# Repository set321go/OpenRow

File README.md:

# OpenRow

A project to design an build an open source rowing computer. This project was born from the idea that I would rather throw something cheaper than a cell phone into the water, a secondary driver was how expensive existing options are given they are in effect a specialized pedometer.

## Goals

1. Hardware and software for an acceleration based rowing computer similar in functionality to a variety of apps available for phones.
2. Speaker/Headset module integration (module provides headset functionality existing computer provides rowing data), which fits into existing headset amplifier form factor.
3. GPS & Bluetooth
4. Fitness platform compatability.

## Secondary Goals

1. Floats
2. Impeller Integration

## Design

This is purely a personal hobby project at some point it may make sense to use a funding platform to do a medium sized run with assembly but there are no plans for this. I have no background in EE.

### Circuit

I have used kicad 5. Its free and open source, you can use whatever tools you wish but you need to ensure the files in the project remain comatible with kicad.

### PCB

The current design is built to [JLCPCB](https://jlcpcb.com/capabilities/Capabilities) 2 layer design rules, I have no solution for providing multiple pcb's which would allow designs for multiple fabrictors. It is likely in the future to ease the design of RF components I will move to a 4 layer design.

### Assembly

Stencil and hand assembly with a homebrew toaster oven reflow setup for prototyping and testing.

### Case

3D printed - in progress

### Software

In progress

## Commercial Use

If you use this project commercially reference to its usage on the consumer device is desired but not required under the licensing terms.

## Getting Involved

If you would like to get involved please get in touch.

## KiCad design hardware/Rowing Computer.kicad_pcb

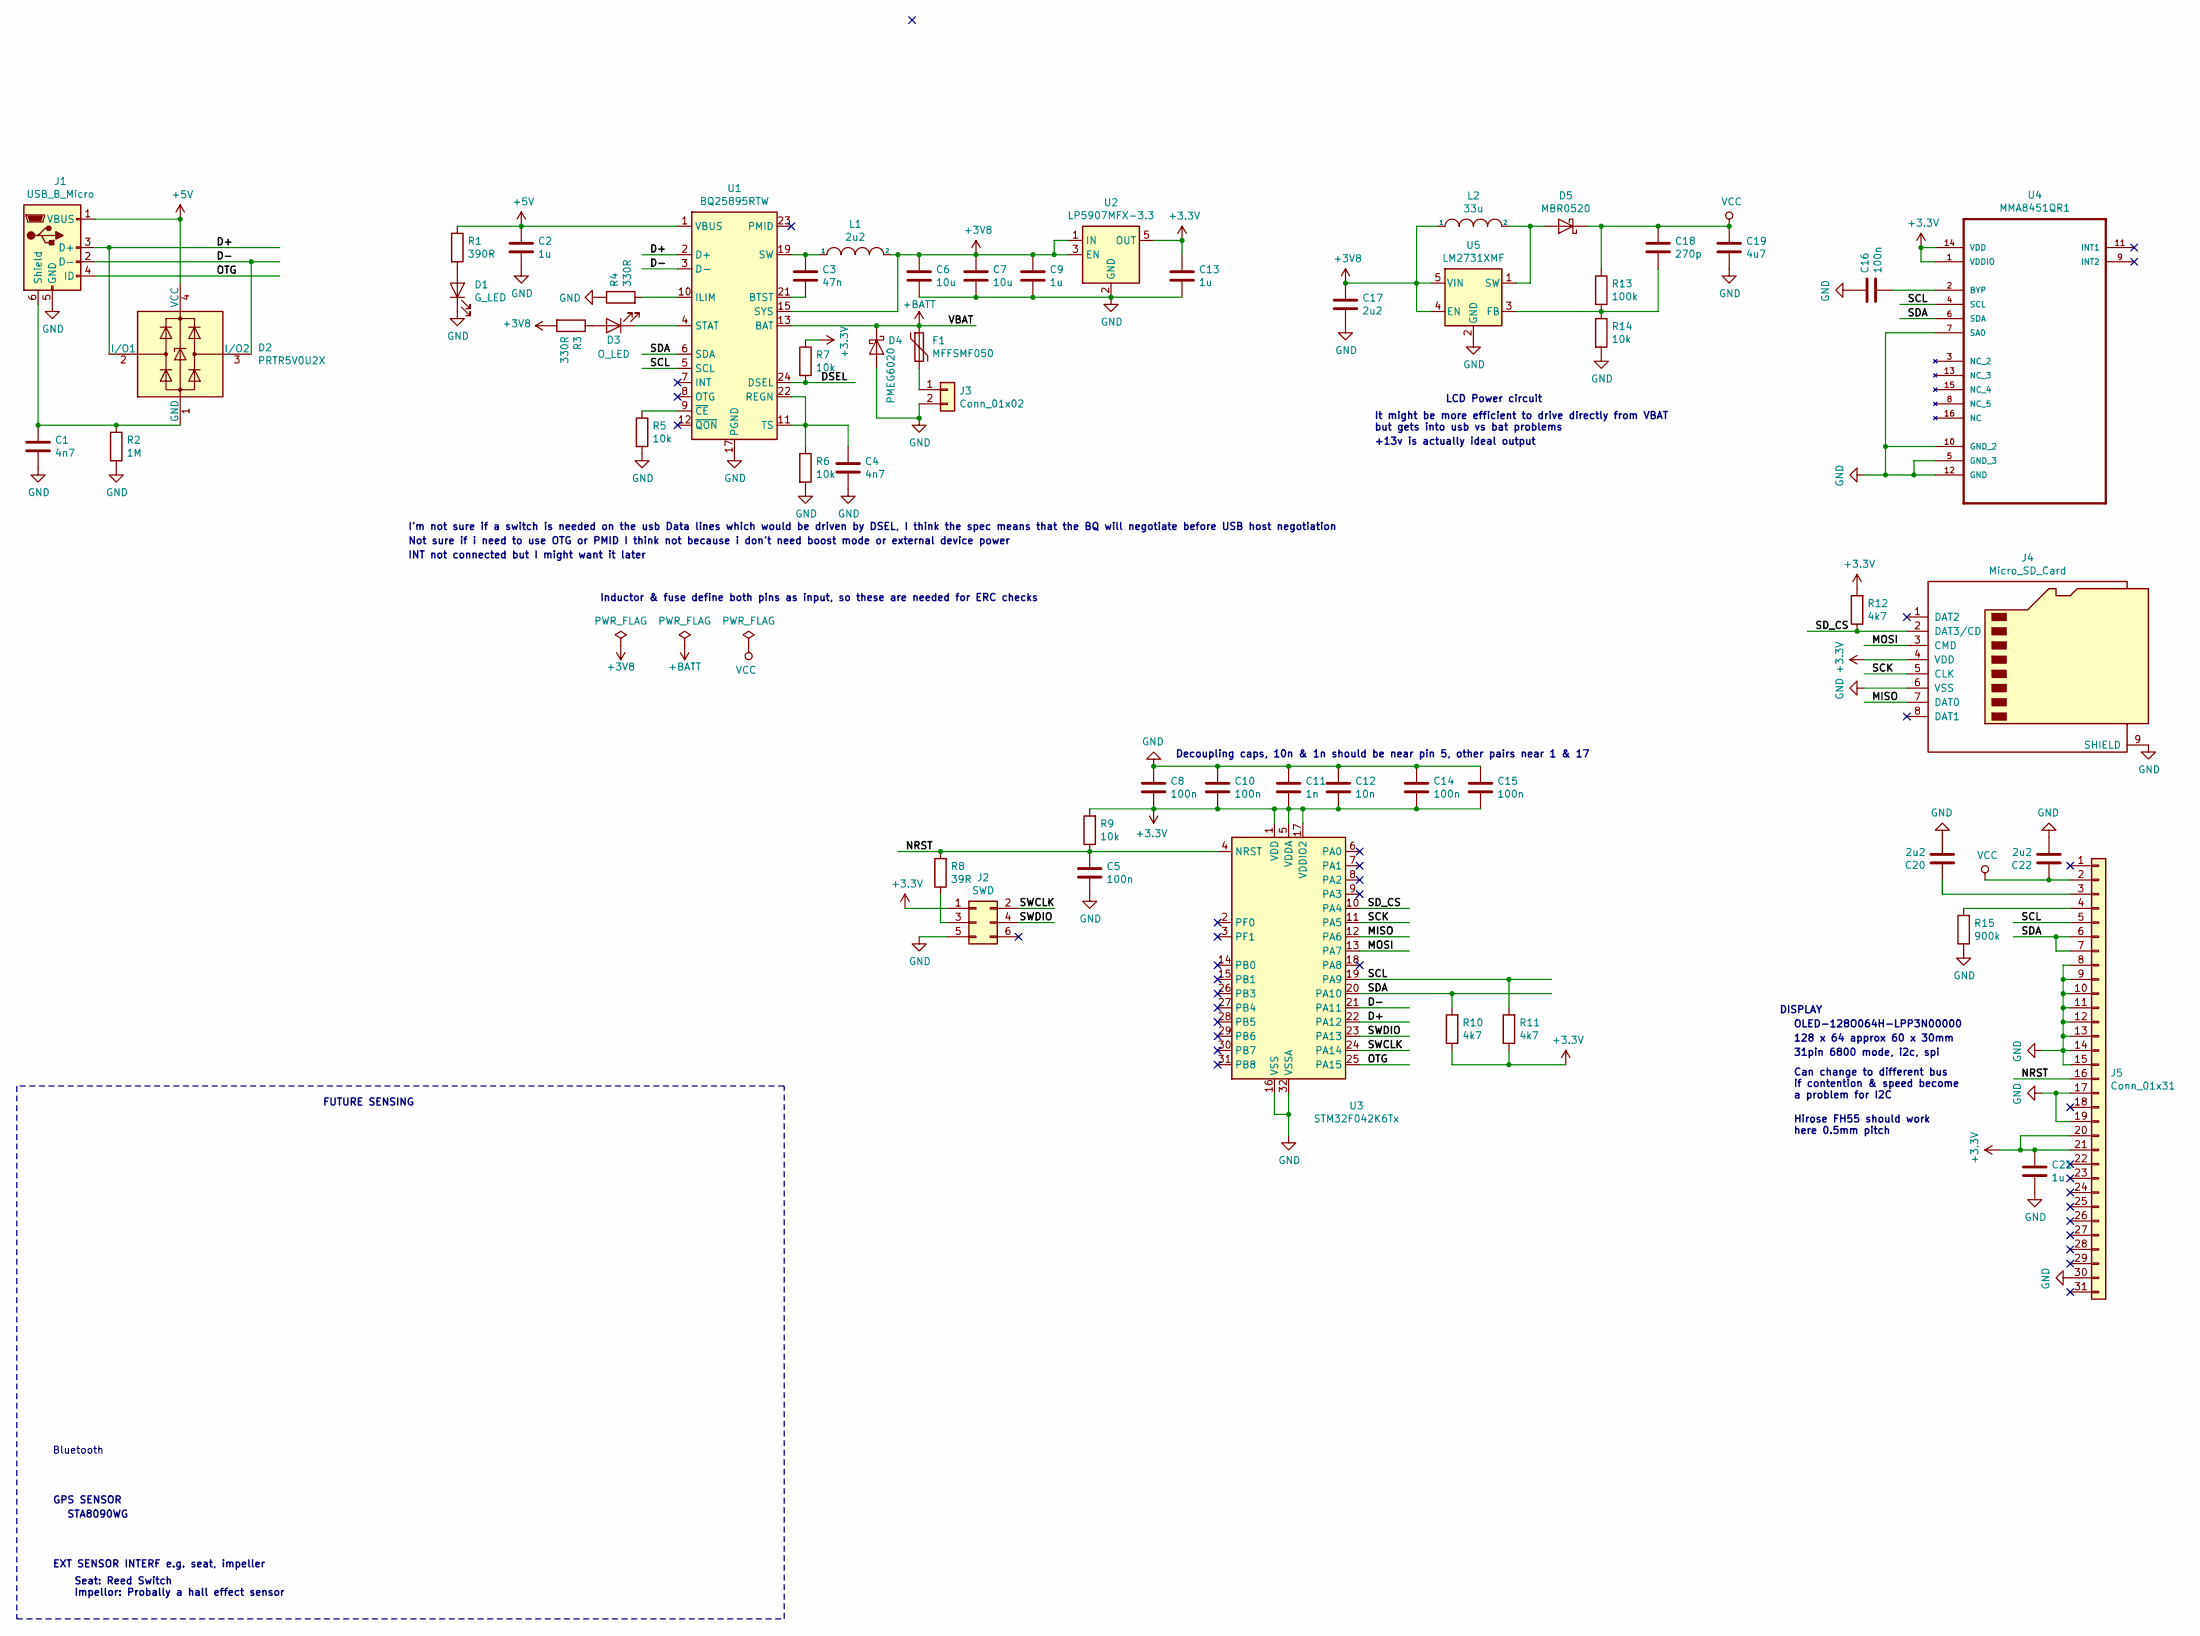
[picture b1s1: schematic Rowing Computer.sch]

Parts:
C1, C4: 4n7; C_0402_1005Metric
C2, C9, C13, C21: 1u; C_0402_1005Metric
C3: 47n; C_0402_1005Metric
C5, C8, C10, C14, C15, C16: 100n; C_0402_1005Metric
C6, C7: 10u; C_0603_1608Metric
C11: 1n; C_0402_1005Metric
C12: 10n; C_0402_1005Metric
C17, C20, C22: 2u2; C_0402_1005Metric
C18: 270p; C_0402_1005Metric
C19: 4u7; C_0603_1608Metric
D1: G_LED; LED_0402_1005Metric
D2: PRTR5V0U2X; SOT-143
D3: O_LED; LED_0402_1005Metric
D4: PMEG6020; D_SOD-123
D5: MBR0520; D_SOD-123
F1: MFFSMF050; Fuse_0402_1005Metric
J1: USB_B_Micro; USB_Micro-B_Molex_47346-0001
J2: SWD; PinHeader_2x03_P1.27mm_Vertical_SMD
J3: Conn_01x02; JST_PH_S2B-PH-SM4-TB_1x02-1MP_P2.00mm_Horizontal
J4: Micro_SD_Card; microSD_HC_Hirose_DM3D-SF
J5: Conn_01x31; FPC_31
L1: 2u2; L_0805_2012Metric
L2: 33u; L_0805_2012Metric
R1: 390R; R_0402_1005Metric
R2: 1M; R_0402_1005Metric
R3, R4: 330R; R_0402_1005Metric
R5, R6, R7, R9, R14: 10k; R_0402_1005Metric
R8: 39R; R_0402_1005Metric
R10, R11, R12: 4k7; R_0402_1005Metric
R13: 100k; R_0402_1005Metric
R15: 900k; R_0402_1005Metric
U1: BQ25895RTW; Texas_S-PWQFN-N24_EP2.7x2.7mm_ThermalVias
U2: LP5907MFX-3.3; SOT-23-5
U3: STM32F042K6Tx; LQFP-32_7x7mm_P0.8mm
U4: MMA8451QR1; QFN50P300X300X100-16N
U5: LM2731XMF; SOT-23-5

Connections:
+3V3: C8.2, C10.2, C11.2, C12.2, C13.1, C14.2, C15.2, C21.1, J2.1, J4.4 (VDD), J5.20, J5.21, R7.1, R9.2, R10.1, R11.1, R12.2, U2.5 (OUT), U3.1 (VDD), U3.5 (VDDA), U3.17 (VDDIO2), U4.1 (VDDIO), U4.14 (VDD)
+3V8: C6.1, C7.1, C9.1, C17.1, L1.2, L2.1, R3.2, U1.15 (SYS), U1.16 (SYS), U2.1 (IN), U2.3 (EN), U5.4 (EN), U5.5 (VIN)
+5V: C2.1, D2.4 (VCC), J1.1 (VBUS), R1.1, U1.1 (VBUS)
+BATT: D4.1 (K), F1.1, U1.13 (BAT), U1.14 (BAT)
/D+: D2.2 (I/O1), J1.3 (D+), U1.2 (D+), U3.22 (PA12)
/D-: D2.3 (I/O2), J1.2 (D-), U1.3 (D-), U3.21 (PA11)
/DSEL: R7.2, U1.24 (DSEL)
/MISO: J4.7 (DAT0), U3.12 (PA6)
/MOSI: J4.3 (CMD), U3.13 (PA7)
/NRST: C5.1, J5.16, R8.2, R9.1, U3.4 (NRST)
/OTG: J1.4 (ID), U3.25 (PA15)
/SCK: J4.5 (CLK), U3.11 (PA5)
/SCL: J5.5, R11.2, U1.5 (SCL), U3.19 (PA9), U4.4 (SCL)
/SDA: J5.6, J5.7, R10.2, U1.6 (SDA), U3.20 (PA10), U4.6 (SDA)
/SD_CS: J4.2 (DAT3/CD), R12.1, U3.10 (PA4)
/SWCLK: J2.2, U3.24 (PA14)
/SWDIO: J2.4, U3.23 (PA13)
GND: C1.2, C2.2, C4.2, C5.2, C6.2, C7.2, C8.1, C9.2, C10.1, C11.1, C12.1, C13.2, C14.1, C15.1, C16.1, C17.2, C19.2, C20.2, C21.2, C22.2, D1.1 (K), D4.2 (A), J1.5 (GND), J2.5, J3.2, J4.6 (VSS), J4.9 (SHIELD), J5.8, J5.9, J5.10, J5.11, J5.12, J5.13, J5.14, J5.15, J5.17, J5.19, J5.30, R2.2, R4.1, R5.2, R6.2, R14.2, R15.1, U1.17 (PGND), U1.18 (PGND), U1.25 (PGND), U2.2 (GND), U3.16 (VSS), U3.32 (VSSA), U4.5 (GND_3), U4.7 (SA0), U4.10 (GND_2), U4.12 (GND), U5.2 (GND)
unnamed: C1.1, D2.1 (GND), J1.6 (Shield), R2.1
unnamed: C3.1, L1.1, U1.19 (SW), U1.20 (SW)
unnamed: C3.2, U1.21 (BTST)
unnamed: C4.1, R6.1, U1.11 (TS), U1.22 (REGN)
unnamed: C16.2, U4.2 (BYP)
unnamed: C18.2, R13.2, R14.1, U5.3 (FB)
unnamed: C20.1, J5.3
unnamed: D1.2 (A), R1.2
unnamed: D3.1 (K), U1.4 (STAT)
unnamed: D3.2 (A), R3.1
unnamed: D5.2 (A), L2.2, U5.1 (SW)
unnamed: F1.2, J3.1
unnamed: J2.3, R8.1
unnamed: J5.4, R15.2
unnamed: R4.2, U1.10 (ILIM)
unnamed: R5.1, U1.9 (~CE)
VCC: C18.1, C19.1, C22.1, D5.1 (K), J5.2, R13.1

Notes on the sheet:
I’m not sure if a switch is needed on the usb Data lines which would be driven by DSEL, I think the spec means that the BQ will negotiate before USB host negotiation
Not sure if i need to use OTG or PMID I think not because i don’t need boost mode or external device power
INT not connected but I might want it later
Decoupling caps, 10n & 1n should be near pin 5, other pairs near 1 & 17
Inductor & fuse define both pins as input, so these are needed for ERC checks
GPS SENSOR
EXT SENSOR INTERF e.g. seat, impeller
DISPLAY
OLED-128O064H-LPP3N00000
128 x 64 approx 60 x 30mm
31pin 6800 mode, i2c, spi
LCD Power circuit
It might be more efficient to drive directly from VBAT but gets into usb vs bat problems
+13v is actually ideal output
Can change to different bus if contention & speed become a problem for I2C
Seat: Reed Switch Impellor: Probally a hall effect sensor
STA8090WG
FUTURE SENSING
Hirose FH55 should work here 0.5mm pitch
Bluetooth

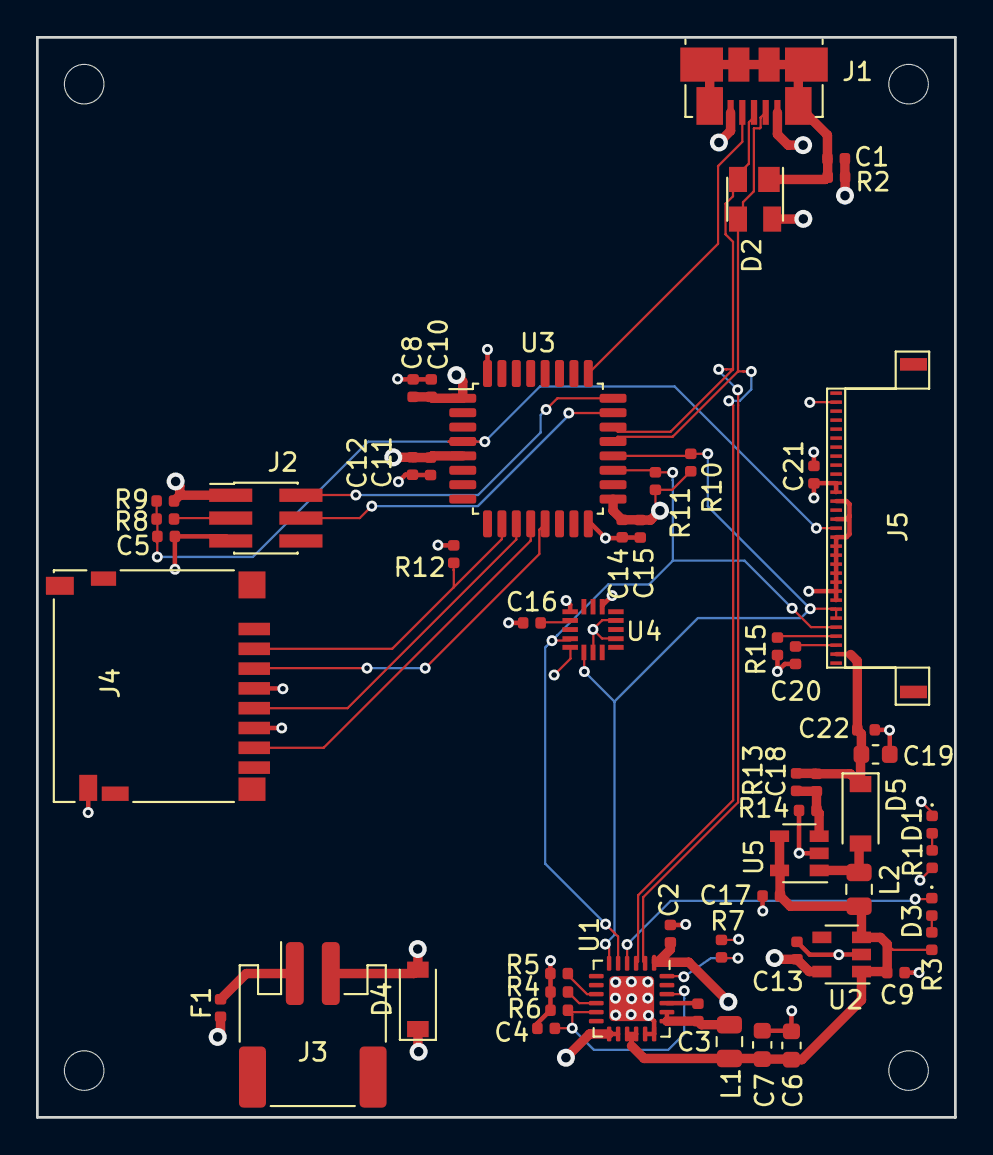
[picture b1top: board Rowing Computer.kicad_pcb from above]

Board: 4 copper layers, 51.0 x 60.0 mm, 55 parts (0 on the bottom side), 35 nets.

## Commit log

2019-05-02 iteration 2 of board with correct footprint sizes and fixes where solder mask was not applied between pads
2019-05-05 Four layer design
